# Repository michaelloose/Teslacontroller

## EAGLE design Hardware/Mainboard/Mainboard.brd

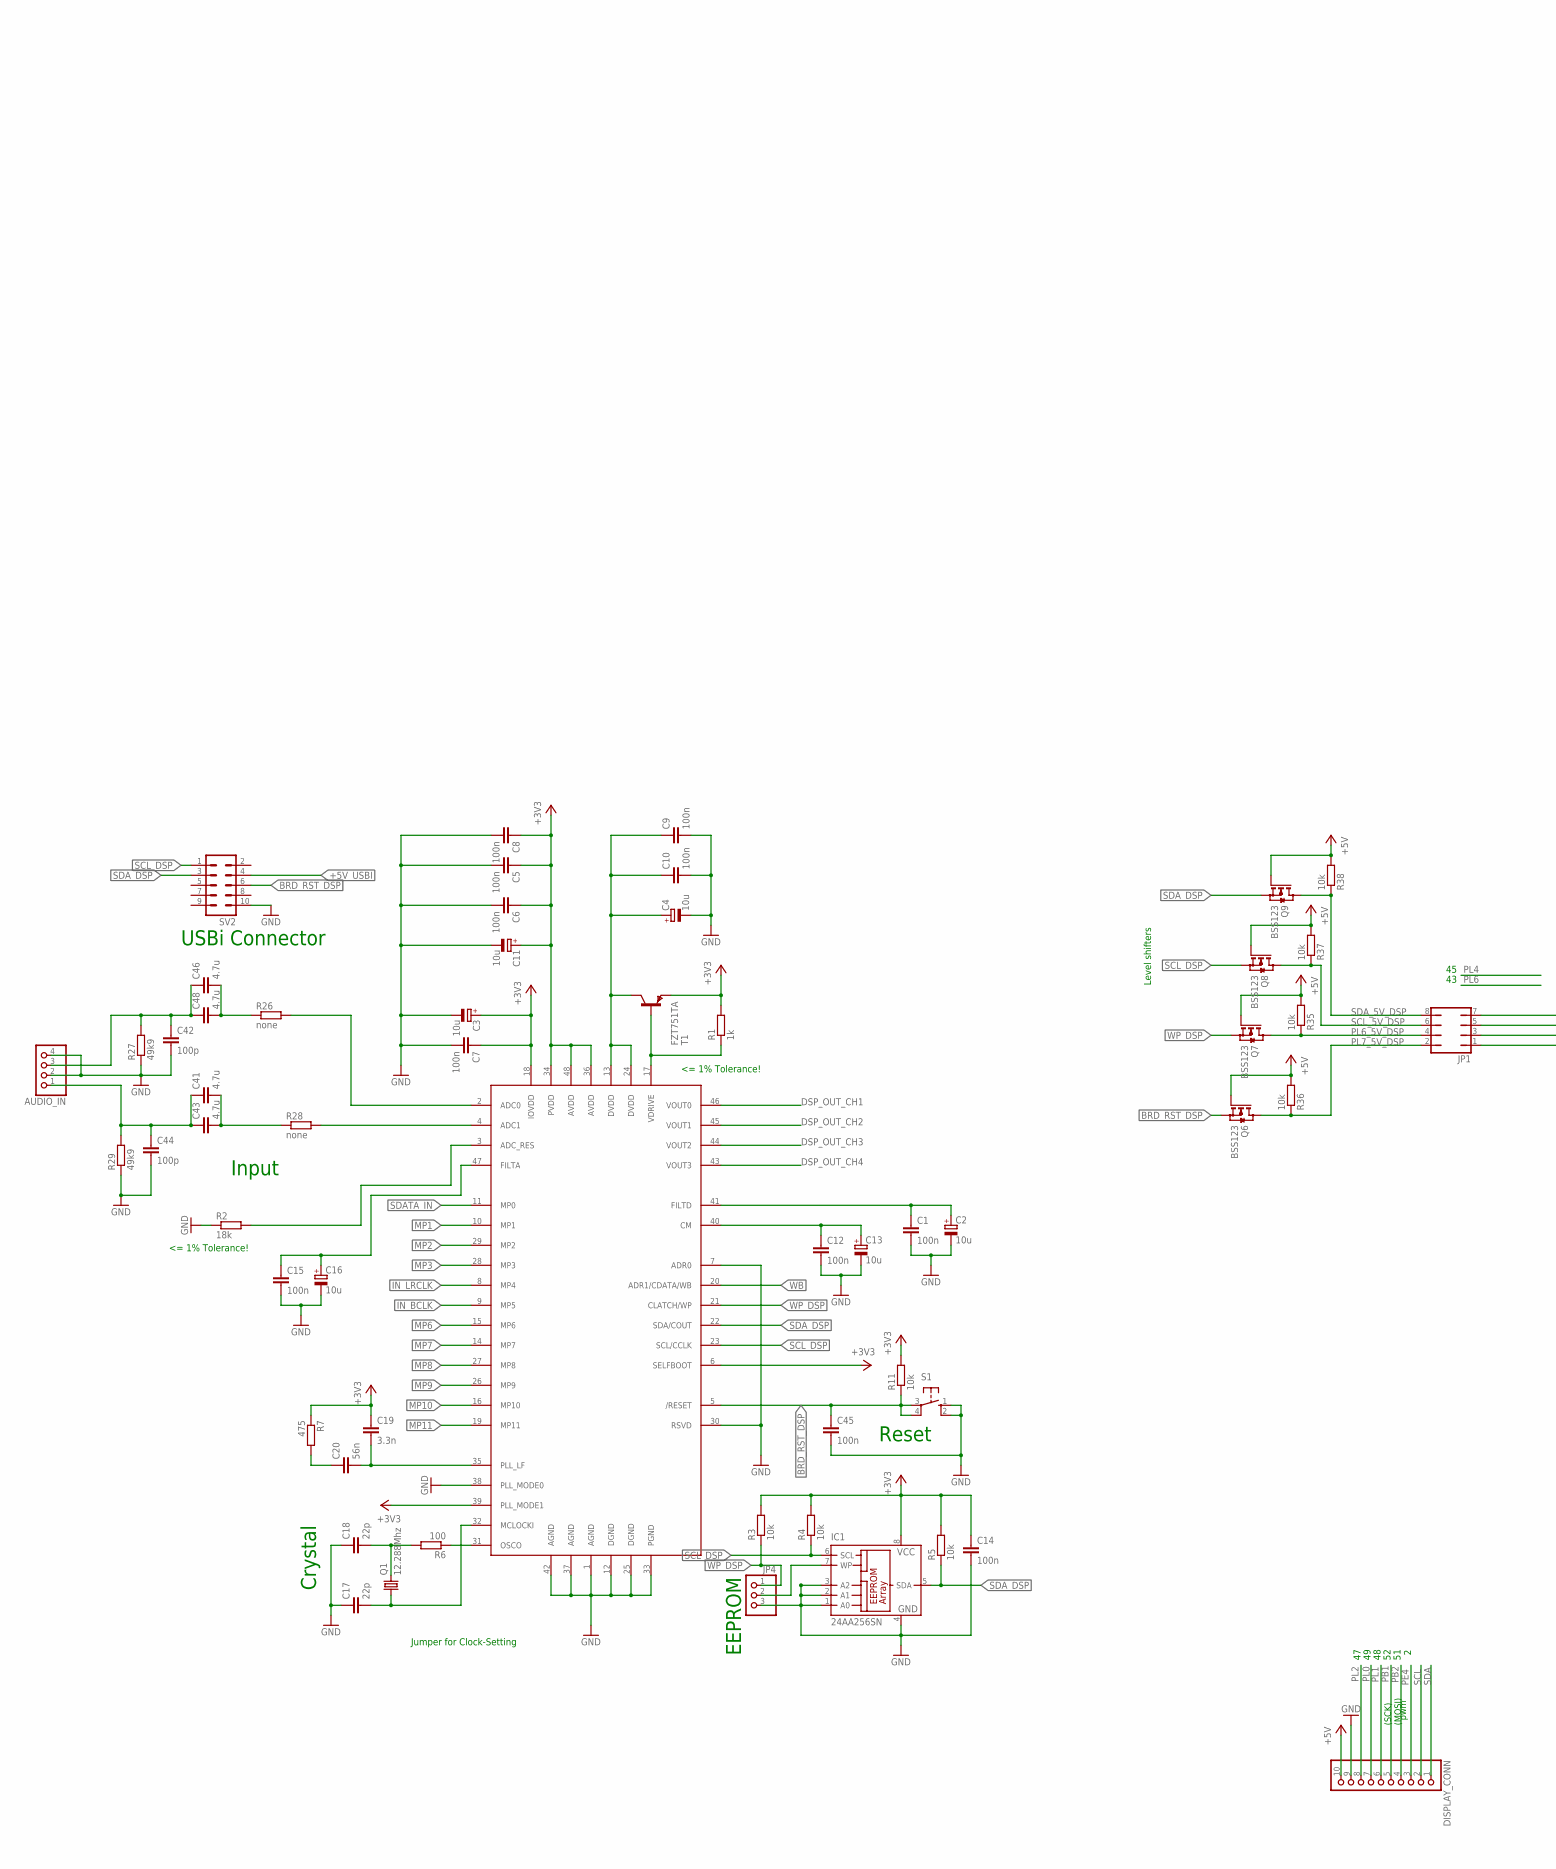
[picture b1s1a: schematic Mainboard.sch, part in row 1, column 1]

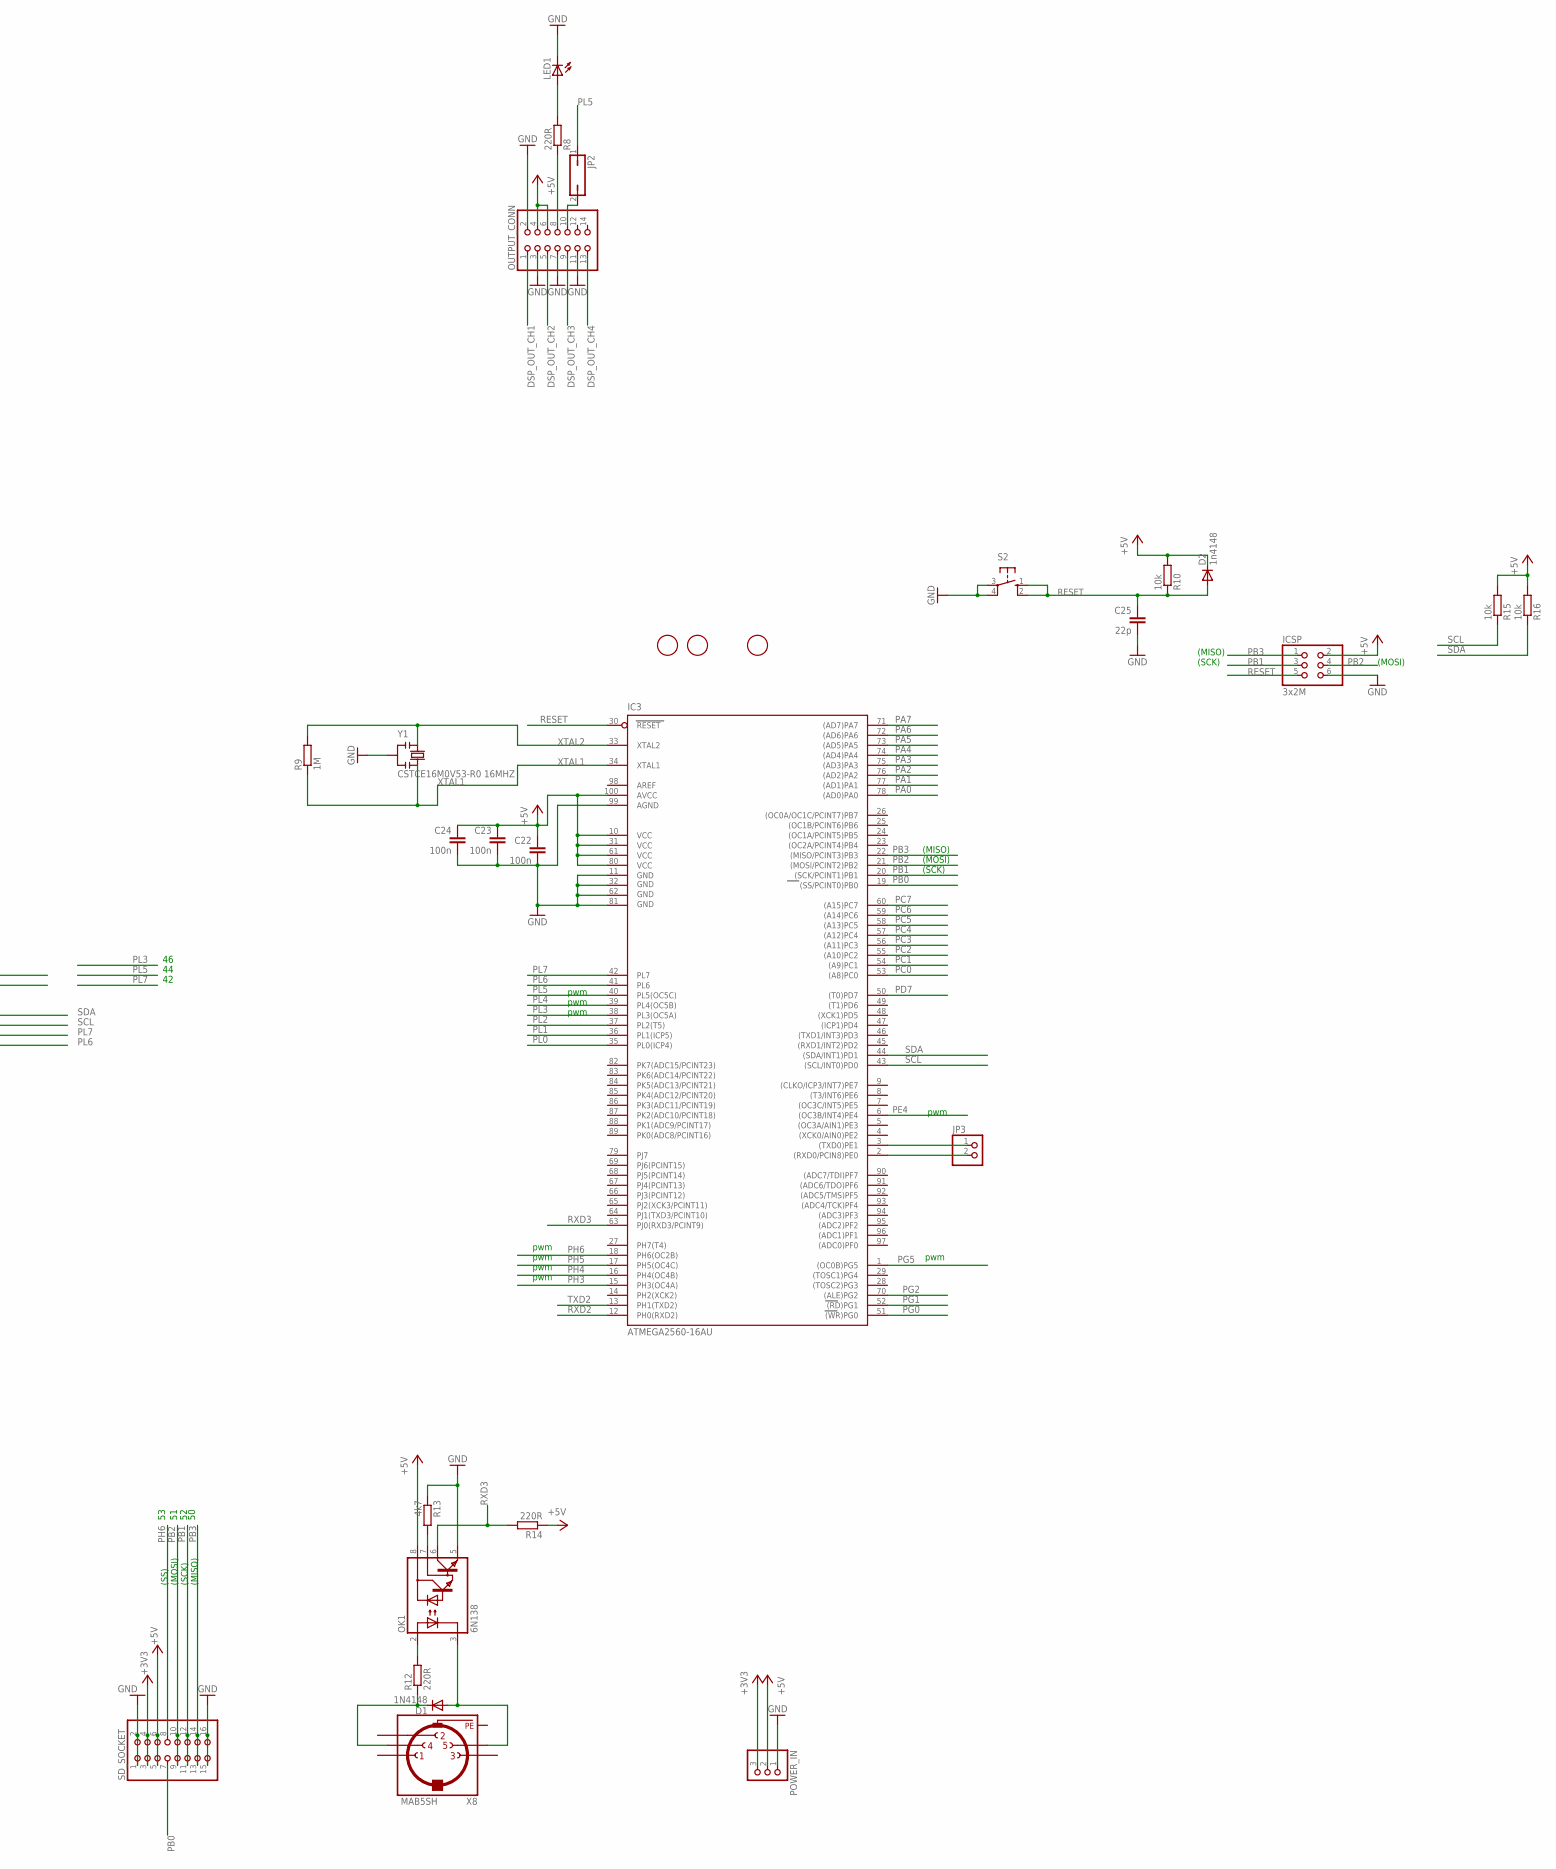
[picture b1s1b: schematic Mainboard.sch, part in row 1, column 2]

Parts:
AUDIO_IN: PINHD-1X4; 1X04
C1, C5, C6, C7, C8, C9, C10, C12, C14, C15, C22, C23, C24, C45: 100n; C0805K
C2, C3, C4, C11, C13, C16: 10u; E1,8-4
C17, C18, C25: 22p; C0805K
C19: 3.3n; C0805K
C20: 56n; C0805K
C41, C43, C46, C48: 4.7u; C050-075X075
C42, C44: 100p; C0805K
D1: 1N4148; SOD-123_MINI-SMA
D2: 1n4148; SOD-123_MINI-SMA
DISPLAY_CONN: PINHD-1X10; 1X10
FD1, FD2, FD4: FIDUCIALMOUNT; FIDUCIA-MOUNT
IC1: 24AA256SN; SO-08
IC3: ATMEGA2560-16AU; TQFP100
ICSP: 3x2M; 2X03
JP1: JP4Q
JP2: JP1Q; JP1
JP3: PINHD-1X2; 1X02
JP4: PINHD-1X3; 1X03
LED1: LED5MM
OK1: 6N138; DIL08
OUTPUT_CONN: PINHD-2X7; 2X07
POWER_IN: PINHD-1X3; 1X03
Q1: 12.288Mhz; HC49/S
Q6, Q7, Q8, Q9: BSS123; SOT23
R1: 1k; R0805
R2: 18k; R0805
R3, R4, R5, R10, R11, R15, R16, R35, R36, R37, R38: 10k; R0805
R6: 100; R0805
R7: 475; R0805
R8, R12, R14: 220R; R0805
R9: 1M; R0805
R13: 4k7; R0805
R26, R28: none; R0805
R27, R29: 49k9; R0805
S1, S2: 10-XX; B3F-10XX
SD_SOCKET: PINHD-2X8; 2X08
SV2: ML10
T1: FZT751TA; SOT223
U$1: ADAU1701; LQFP-48
X8: MAB5SH
Y1: CSTCE16M0V53-R0 16MHZ; RESONATOR

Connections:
1V8_DSP: C4.+, C9.1, C10.1, T1.2 (C), T1.4 (C), U$1.13 (DVDD), U$1.24 (DVDD)
+3V3: C3.+, C5.1, C6.1, C7.1, C8.1, C11.+, C14.1, C19.1, IC1.8 (VCC), POWER_IN.3, R1.2, R3.2, R4.2, R5.2, R7.1, R11.2, SD_SOCKET.3, SD_SOCKET.4, T1.3 (E), U$1.6 (SELFBOOT), U$1.18 (IOVDD), U$1.34 (PVDD), U$1.36 (AVDD), U$1.39 (PLL_MODE1), U$1.48 (AVDD)
+5V: C22.1, C23.1, C24.1, D2.C, DISPLAY_CONN.10, IC3.10 (VCC), IC3.31 (VCC1), IC3.61 (VCC2), IC3.80 (VCC3), IC3.100 (AVCC), ICSP.2, OK1.8 (VCC), OUTPUT_CONN.4, OUTPUT_CONN.6, POWER_IN.2, Q6.1 (G), Q7.1 (G), Q8.1 (G), Q9.1 (G), R10.2, R14.1, R15.2, R16.2, R35.2, R36.2, R37.2, R38.2, SD_SOCKET.5, SD_SOCKET.6
+5V_USBI: SV2.4
ADC0: R28.2, U$1.4 (ADC1)
BRD_RST_DSP: C45.1, Q6.2 (S), R11.1, S1.3, S1.4 (P1), SV2.6, U$1.5 (/RESET)
CM: C12.1, C13.+, U$1.40 (CM)
DSP_OUT_CH1: OUTPUT_CONN.1, U$1.46 (VOUT0)
DSP_OUT_CH2: OUTPUT_CONN.5, U$1.45 (VOUT1)
DSP_OUT_CH3: OUTPUT_CONN.9, U$1.44 (VOUT2)
DSP_OUT_CH4: OUTPUT_CONN.13, U$1.43 (VOUT3)
FILTA: C15.1, C16.+, U$1.47 (FILTA)
FILTD: C1.1, C2.+, U$1.41 (FILTD)
GND: AUDIO_IN.2, AUDIO_IN.4, C1.2, C2.-, C3.-, C4.-, C5.2, C6.2, C7.2, C8.2, C9.2, C10.2, C11.-, C12.2, C13.-, C14.2, C15.2, C16.-, C17.1, C18.1, C22.2, C23.2, C24.2, C25.2, C42.2, C44.2, C45.2, DISPLAY_CONN.9, IC1.1 (A0), IC1.2 (A1), IC1.3 (A2), IC1.4 (GND), IC3.11 (GND), IC3.32 (GND1), IC3.62 (GND2), IC3.81 (GND3), IC3.99 (AGND), ICSP.6, JP4.3, LED1.K (C), OK1.5 (GND), OUTPUT_CONN.2, OUTPUT_CONN.3, OUTPUT_CONN.7, OUTPUT_CONN.11, POWER_IN.1, R2.1, R13.1, R27.1, R29.1, S1.1 (S), S1.2 (S1), S2.3, S2.4 (P1), SD_SOCKET.1, SD_SOCKET.2, SD_SOCKET.15, SD_SOCKET.16, SV2.10, U$1.1 (AGND), U$1.7 (ADR0), U$1.12 (DGND), U$1.25 (DGND), U$1.30 (RSVD), U$1.33 (PGND), U$1.37 (AGND), U$1.38 (PLL_MODE0), U$1.42 (AGND), Y1.2
IN_BCLK: U$1.9 (MP5)
IN_LRCLK: U$1.8 (MP4)
MP1: U$1.10 (MP1)
MP2: U$1.29 (MP2)
MP3: U$1.28 (MP3)
MP6: U$1.15 (MP6)
MP7: U$1.14 (MP7)
MP8: U$1.27 (MP8)
MP9: U$1.26 (MP9)
MP10: U$1.16 (MP10)
MP11: U$1.19 (MP11)
unnamed: R2.2, U$1.3 (ADC_RES)
unnamed: R1.1, T1.1 (B), U$1.17 (VDRIVE)
unnamed: C19.2, C20.2, U$1.35 (PLL_LF)
unnamed: OUTPUT_CONN.8, R8.1
unnamed: C20.1, R7.2
unnamed: C18.2, Q1.2, R6.2
unnamed: C17.2, Q1.1, U$1.32 (MCLOCKI)
unnamed: R6.1, U$1.31 (OSCO)
unnamed: LED1.A, R8.2
unnamed: JP2.2, OUTPUT_CONN.10
unnamed: IC3.3 ((TXD0)PE1), JP3.1
unnamed: IC3.2 ((RXD0/PCIN8)PE0), JP3.2
unnamed: OK1.2 (A), R12.2
unnamed: D1.C, R12.1, X8.4
unnamed: D1.A, OK1.3 (C), X8.5
unnamed: OK1.7 (VB), R13.2
unnamed: C46.2, C48.2, R26.1
unnamed: AUDIO_IN.3, C42.1, C46.1, C48.1, R27.2
unnamed: AUDIO_IN.1, C41.1, C43.1, C44.1, R29.2
unnamed: C41.2, C43.2, R28.1
unnamed: R26.2, U$1.2 (ADC0)
unnamed: IC1.7 (WP), JP4.2
PA0: IC3.78 ((AD0)PA0)
PA1: IC3.77 ((AD1)PA1)
PA2: IC3.76 ((AD2)PA2)
PA3: IC3.75 ((AD3)PA3)
PA4: IC3.74 ((AD4)PA4)
PA5: IC3.73 ((AD5)PA5)
PA6: IC3.72 ((AD6)PA6)
PA7: IC3.71 ((AD7)PA7)
PB0: IC3.19 ((SS/PCINT0)PB0), SD_SOCKET.7
PB1: DISPLAY_CONN.5, IC3.20 ((SCK/PCINT1)PB1), ICSP.3, SD_SOCKET.11, SD_SOCKET.12
PB2: DISPLAY_CONN.4, IC3.21 ((MOSI/PCINT2)PB2), ICSP.4, SD_SOCKET.9, SD_SOCKET.10
PB3: IC3.22 ((MISO/PCINT3)PB3), ICSP.1, SD_SOCKET.13, SD_SOCKET.14
PC0: IC3.53 ((A8)PC0)
PC1: IC3.54 ((A9)PC1)
PC2: IC3.55 ((A10)PC2)
PC3: IC3.56 ((A11)PC3)
PC4: IC3.57 ((A12)PC4)
PC5: IC3.58 ((A13)PC5)
PC6: IC3.59 ((A14)PC6)
PC7: IC3.60 ((A15)PC7)
PD7: IC3.50 ((T0)PD7)
PE: X8.PE, X8.PE@ (PE)
PE4: DISPLAY_CONN.3, IC3.6 ((OC3B/INT4)PE4)
PG0: IC3.51 ((WR)PG0)
PG1: IC3.52 ((RD)PG1)
PG2: IC3.70 ((ALE)PG2)
PG5: IC3.1 ((OC0B)PG5)
PH3: IC3.15 (PH3(OC4A))
PH4: IC3.16 (PH4(OC4B))
PH5: IC3.17 (PH5(OC4C))
PH6: IC3.18 (PH6(OC2B)), SD_SOCKET.8
PL0: DISPLAY_CONN.7, IC3.35 (PL0(ICP4))
PL1: DISPLAY_CONN.6, IC3.36 (PL1(ICP5))
PL2: DISPLAY_CONN.8, IC3.37 (PL2(T5))
PL3: IC3.38 (PL3(OC5A))
PL4: IC3.39 (PL4(OC5B))
PL5: IC3.40 (PL5(OC5C)), JP2.1
PL6: IC3.41 (PL6), JP1.1
PL6_5V_DSP: JP1.4, Q7.3 (D), R35.1
PL7: IC3.42 (PL7), JP1.3
PL7_5V_DSP: JP1.2, Q6.3 (D), R36.1
RESET: C25.1, D2.A, IC3.30 (RESET), ICSP.5, R10.1, S2.1 (S), S2.2 (S1)
RXD2: IC3.12 (PH0(RXD2))
RXD3: IC3.63 (PJ0(RXD3/PCINT9)), OK1.6 (VO), R14.2
SCL: DISPLAY_CONN.2, IC3.43 ((SCL/INT0)PD0), JP1.5, R15.1
SCL_5V_DSP: JP1.6, Q8.3 (D), R37.1
SCL_DSP: IC1.6 (SCL), Q8.2 (S), R4.1, SV2.1, U$1.23 (SCL/CCLK)
SDA: DISPLAY_CONN.1, IC3.44 ((SDA/INT1)PD1), JP1.7, R16.1
SDATA_IN: U$1.11 (MP0)
SDA_5V_DSP: JP1.8, Q9.3 (D), R38.1
SDA_DSP: IC1.5 (SDA), Q9.2 (S), R5.1, SV2.3, U$1.22 (SDA/COUT)
TXD2: IC3.13 (PH1(TXD2))
WB: U$1.20 (ADR1/CDATA/WB)
WP_DSP: JP4.1, Q7.2 (S), R3.1, U$1.21 (CLATCH/WP)
XTAL1: IC3.34 (XTAL1), R9.1, Y1.3
XTAL2: IC3.33 (XTAL2), R9.2, Y1.1

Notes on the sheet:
<= 1% Tolerance!
EEPROM
Jumper for Clock-Setting
Crystal
Reset
Input
USBi Connector
Level shifters
(SCK)
(MISO)
(MOSI)
pwm
(SS)

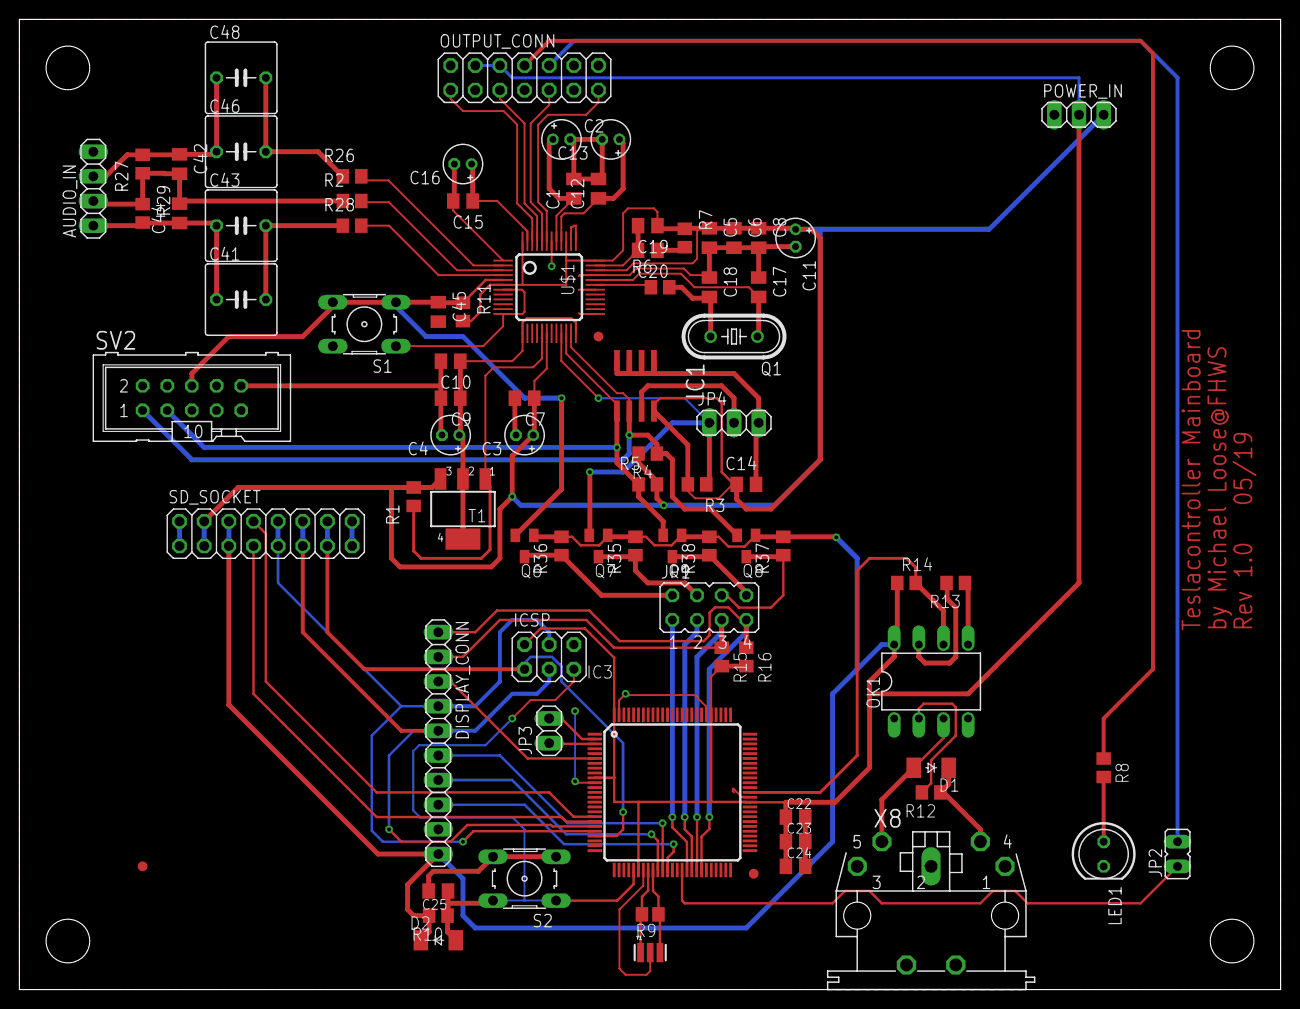
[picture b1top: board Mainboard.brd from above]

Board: 2 copper layers, 130.0 x 100.0 mm, 86 parts (0 on the bottom side), 61 nets.

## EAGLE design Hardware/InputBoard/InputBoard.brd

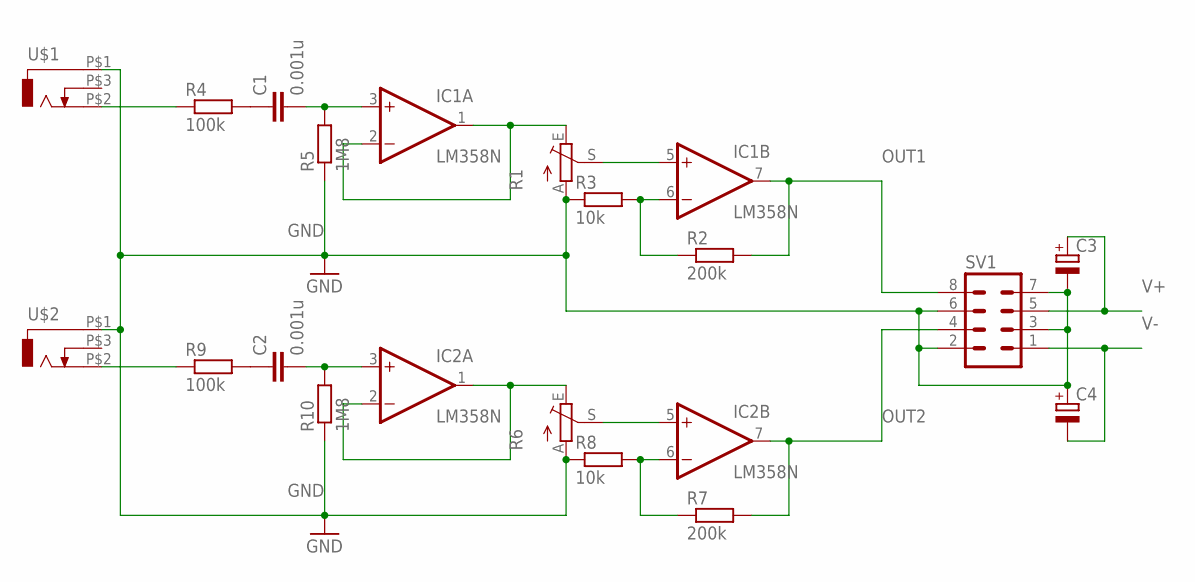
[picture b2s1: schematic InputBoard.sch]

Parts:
C1, C2: 0.001u; C050-025X075
C3, C4: CPOL-EUE5-8.5; E5-8,5
IC1, IC2: LM358N; DIL08
R1, R6: TRIM_EU-CIP20C-6MM; CIP20C-6MM
R2, R7: 200k; 0207/10
R3, R8: 10k; 0207/10
R4, R9: 100k; 0207/10
R5, R10: 1M8; 0207/10
SV1: MA04-2
U$1, U$2: EBS63P

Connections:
GND: C3.-, C4.+, R1.A, R3.1, R5.1, R6.A, R8.1, R10.1, SV1.2, SV1.3, SV1.6, SV1.7, U$1.P$1 (1), U$2.P$1 (1)
unnamed: IC1.1 (OUT), IC1.2 (-IN), R1.E
unnamed: IC1.5 (+IN), R1.S
unnamed: IC1.6 (-IN), R2.1, R3.2
unnamed: C1.2, IC1.3 (+IN), R5.2
unnamed: C1.1, R4.2
unnamed: IC2.1 (OUT), IC2.2 (-IN), R6.E
unnamed: IC2.5 (+IN), R6.S
unnamed: IC2.6 (-IN), R7.1, R8.2
unnamed: C2.2, IC2.3 (+IN), R10.2
unnamed: C2.1, R9.2
unnamed: R9.1, U$2.P$2 (3)
unnamed: R4.1, U$1.P$2 (3)
OUT1: IC1.7 (OUT), R2.2, SV1.8
OUT2: IC2.7 (OUT), R7.2, SV1.4
V+: C3.+, IC1.8 (V+), IC2.8 (V+), SV1.5
V-: C4.-, IC1.4 (V-), IC2.4 (V-), SV1.1

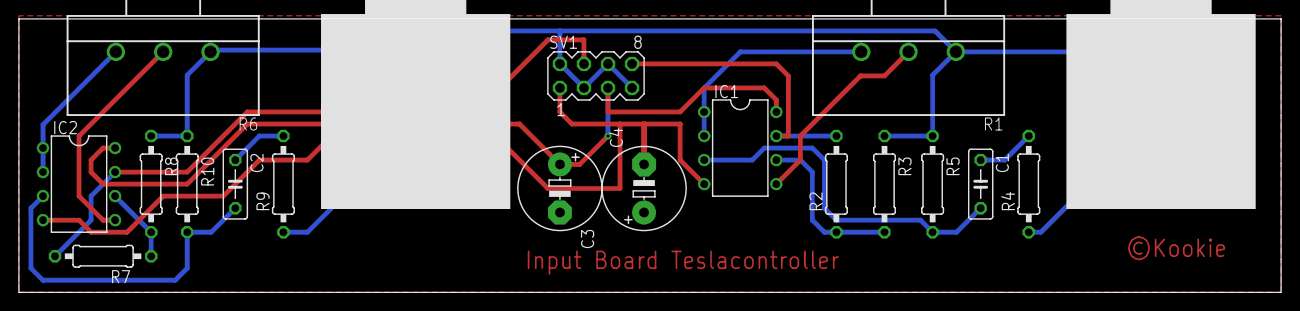
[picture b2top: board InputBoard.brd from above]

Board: 2 copper layers, 133.3 x 28.9 mm, 19 parts (0 on the bottom side), 17 nets.

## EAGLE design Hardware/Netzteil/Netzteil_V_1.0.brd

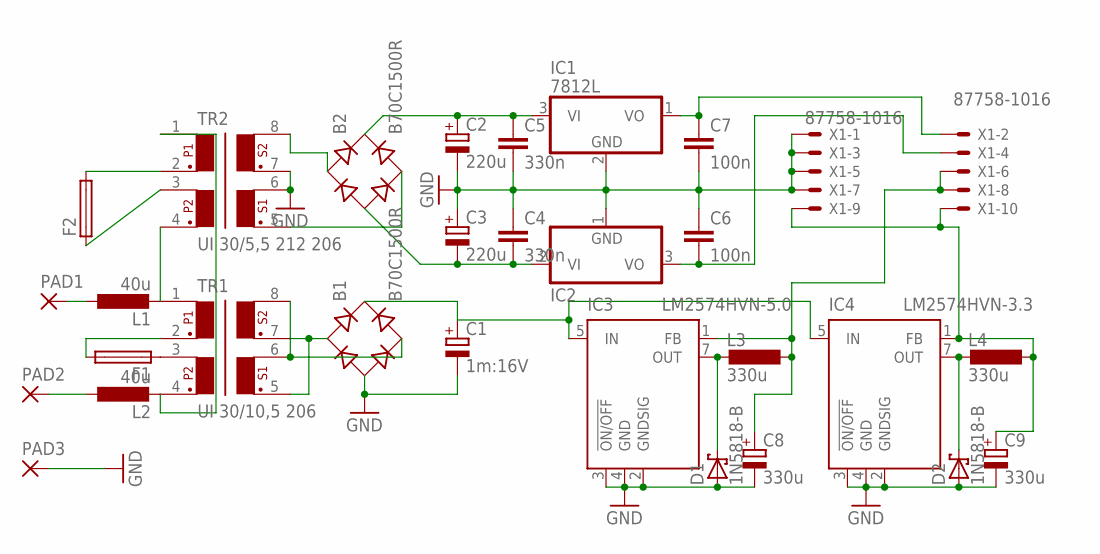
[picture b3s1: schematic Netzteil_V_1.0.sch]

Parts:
B1, B2: B70C1500R; RB1A
C1: 1m:16V; E5-13
C2, C3: 220u; E5-10,5
C4, C5: 330n; C102-064X133
C6: 100n; C102-064X133
C7: 100n; C102-054X133
C8, C9: 330u; E2,5-7
D1, D2: 1N5818-B; DO41-7.6
F1, F2: SH25
IC1: 7812L; TO92
IC2: 7912L; TO92
IC3: LM2574HVN-5.0; DIL08
IC4: LM2574HVN-3.3; DIL08
L1, L2: 40u; IRF24
L3, L4: 330u; 0207/5V
PAD1, PAD2, PAD3: 3,81/1,4
TR1: UI 30/10,5 206; FL02-08
TR2: UI 30/5,5 212 206; FL02-08
X1: 87758-1016

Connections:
3V3: C9.+, IC4.1 (FB), L4.1, X1.9, X1.10
5V: C8.+, IC3.1 (FB), L3.1, X1.6, X1.8
+12V: C7.1, IC1.1 (VO), X1.2
-12V: C6.2, IC2.3 (VO), X1.4
GND: B1.-, C1.-, C2.-, C3.+, C4.1, C5.2, C6.1, C7.2, C8.-, C9.-, D1.A, D2.A, IC1.2 (GND), IC2.1 (GND), IC3.2 (GNDSIG), IC3.3 (!ON/OFF), IC3.4 (GND), IC4.2 (GNDSIG), IC4.3 (!ON/OFF), IC4.4 (GND), PAD3.1, TR2.6, TR2.7, X1.1, X1.3, X1.5, X1.7
unnamed: F1.1, TR1.3
unnamed: F1.2, TR1.2
unnamed: B1.AC1, TR1.5, TR1.7
unnamed: B1.AC2, TR1.6, TR1.8
unnamed: B1.+, C1.+, IC3.5 (IN), IC4.5 (IN)
unnamed: B2.-, C3.-, C4.2, IC2.2 (VI)
unnamed: L1.2, TR1.1, TR2.4
unnamed: L2.2, TR1.4, TR2.1
unnamed: D1.C, IC3.7 (OUT), L3.2
unnamed: B2.AC1, TR2.8
unnamed: B2.AC2, TR2.5
unnamed: B2.+, C2.+, C5.1, IC1.3 (VI)
unnamed: F2.1, TR2.3
unnamed: F2.2, TR2.2
unnamed: D2.C, IC4.7 (OUT), L4.2
unnamed: L1.1, PAD1.1
unnamed: L2.1, PAD2.1

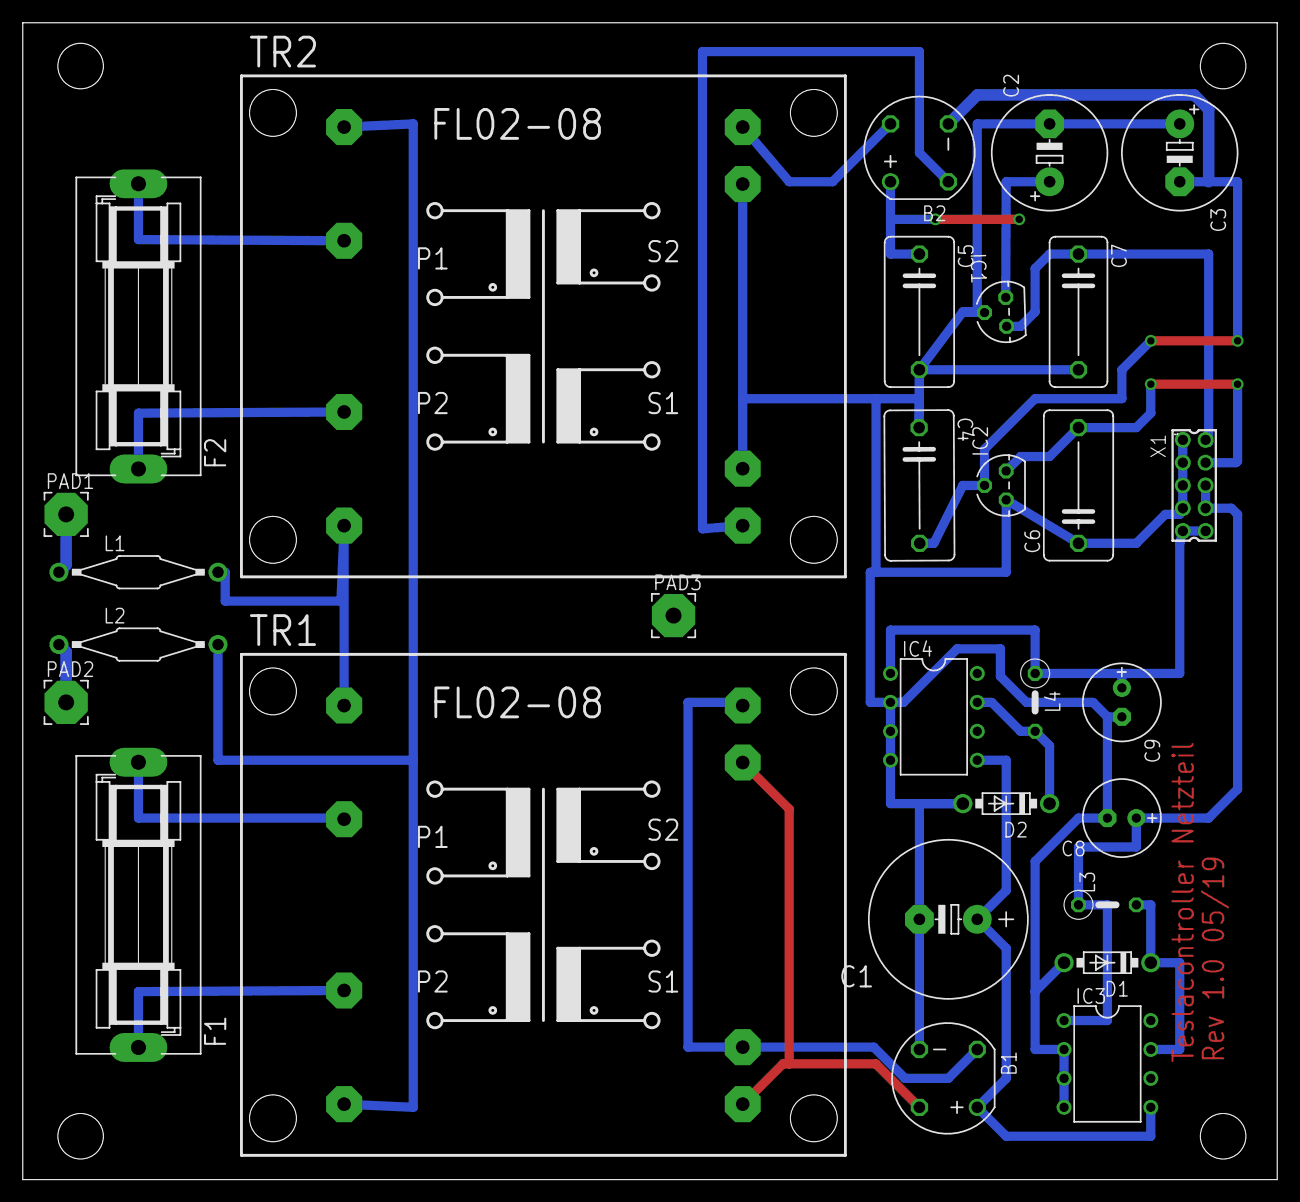
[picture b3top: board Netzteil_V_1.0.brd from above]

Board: 2 copper layers, 110.2 x 101.6 mm, 29 parts (0 on the bottom side), 22 nets.

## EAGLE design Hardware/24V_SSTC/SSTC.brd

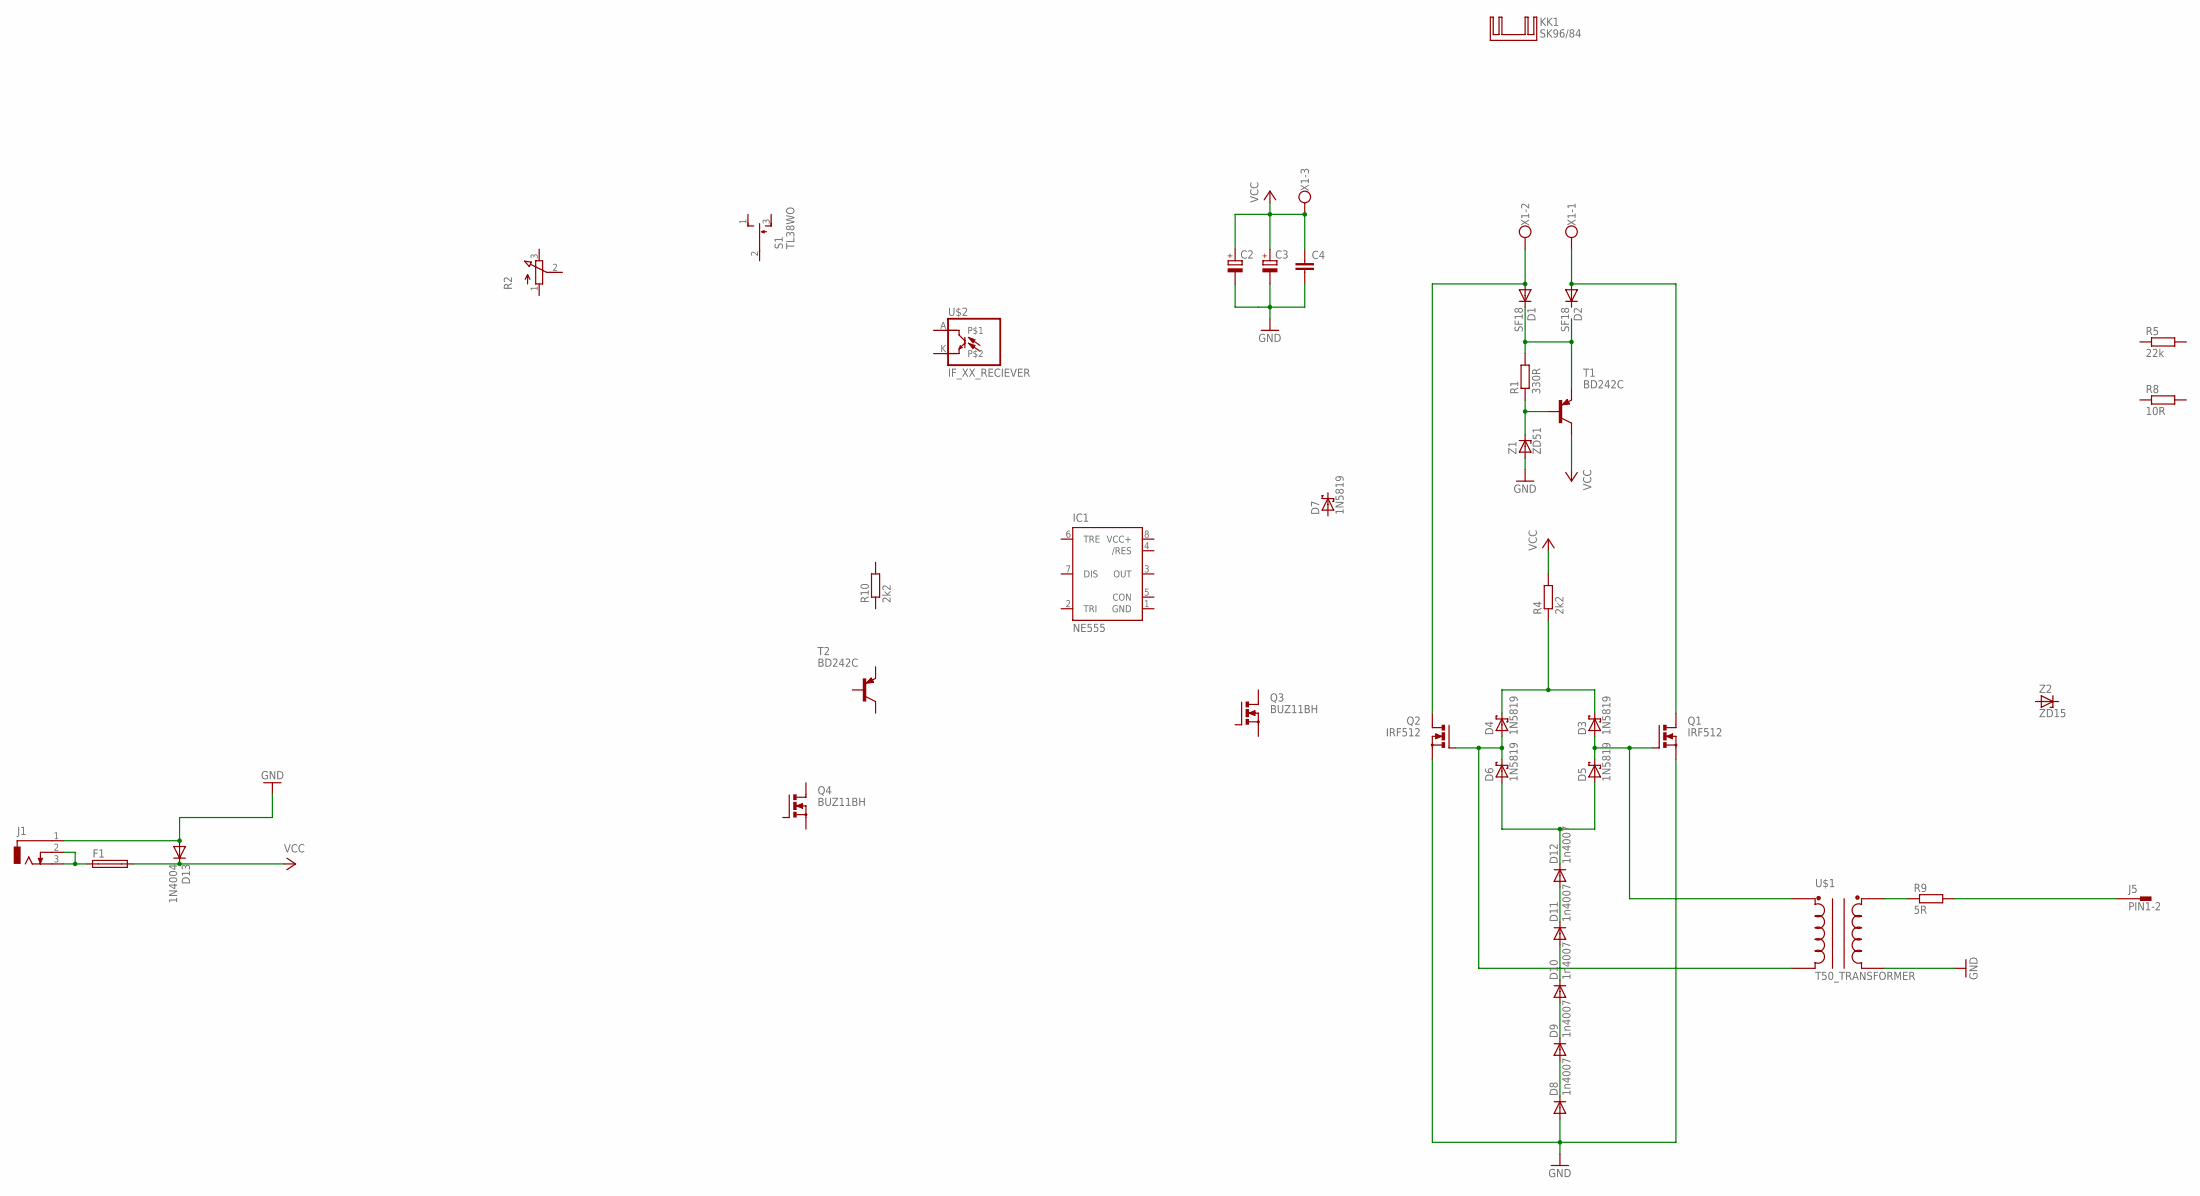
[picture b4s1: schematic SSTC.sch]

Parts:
C2, C3: CPOL-EUE7.5-18; E7,5-18
C4: C-EU150-072X183; C150-072X183
D1, D2: SF18; DO41-7.6
D3, D4, D5, D6, D7: 1N5819; SMB
D8, D9, D10, D11, D12: 1n4007; MELF-MLL41
D13: 1N4004; DO41-10
F1: SH22,5A
IC1: NE555; DIL-08
J1: DCJ0303
J5: PIN1-2; 62221
KK1: SK96/84
Q1, Q2: IRF512; TO220BV
Q3, Q4: BUZ11BH; TO220BH
R1: 330R; R2512
R2: 3RP/1610N
R4, R10: 2k2; R2512
R5: 22k; R2512
R8: 10R; R2512
R9: 5R; 0309/12
S1: TL38WO; TL3XWO
T1, T2: BD242C; TO220V
U$1: T50_TRANSFORMER
U$2: IF_XX_RECIEVER; IF_XX
X1: W237-103
Z1: ZD51; SOD80C
Z2: ZD15; SOD80C

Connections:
GND: C2.-, C3.-, C4.2, D8.A, D13.A, IC1.1 (GND), J1.1, Q1.S, Q2.S, U$1.C2A, Z1.A
unnamed: D8.C, D9.A
unnamed: D9.C, D10.A
unnamed: D10.C, D11.A
unnamed: D11.C, D12.A
unnamed: D5.A, D6.A, D12.C
unnamed: D4.A, D6.C, Q2.G, U$1.C1A
unnamed: D3.A, D5.C, Q1.G, U$1.C1B
unnamed: D1.A, Q2.D, X1.2
unnamed: D2.A, Q1.D, X1.1
unnamed: D3.C, D4.C, R4.1
unnamed: D1.C, R1.2, T1.3 (E)
unnamed: R1.1, T1.1 (B), Z1.C
unnamed: R9.1, U$1.C2B
unnamed: J5.1, R9.2
unnamed: F1.1, J1.2, J1.3
VCC: C2.+, C3.+, C4.1, D13.C, F1.2, R4.2, T1.2 (C), X1.3
VCC+: IC1.8 (VCC+)

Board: 2 copper layers, 40 parts (0 on the bottom side), 17 nets, no tracks yet.

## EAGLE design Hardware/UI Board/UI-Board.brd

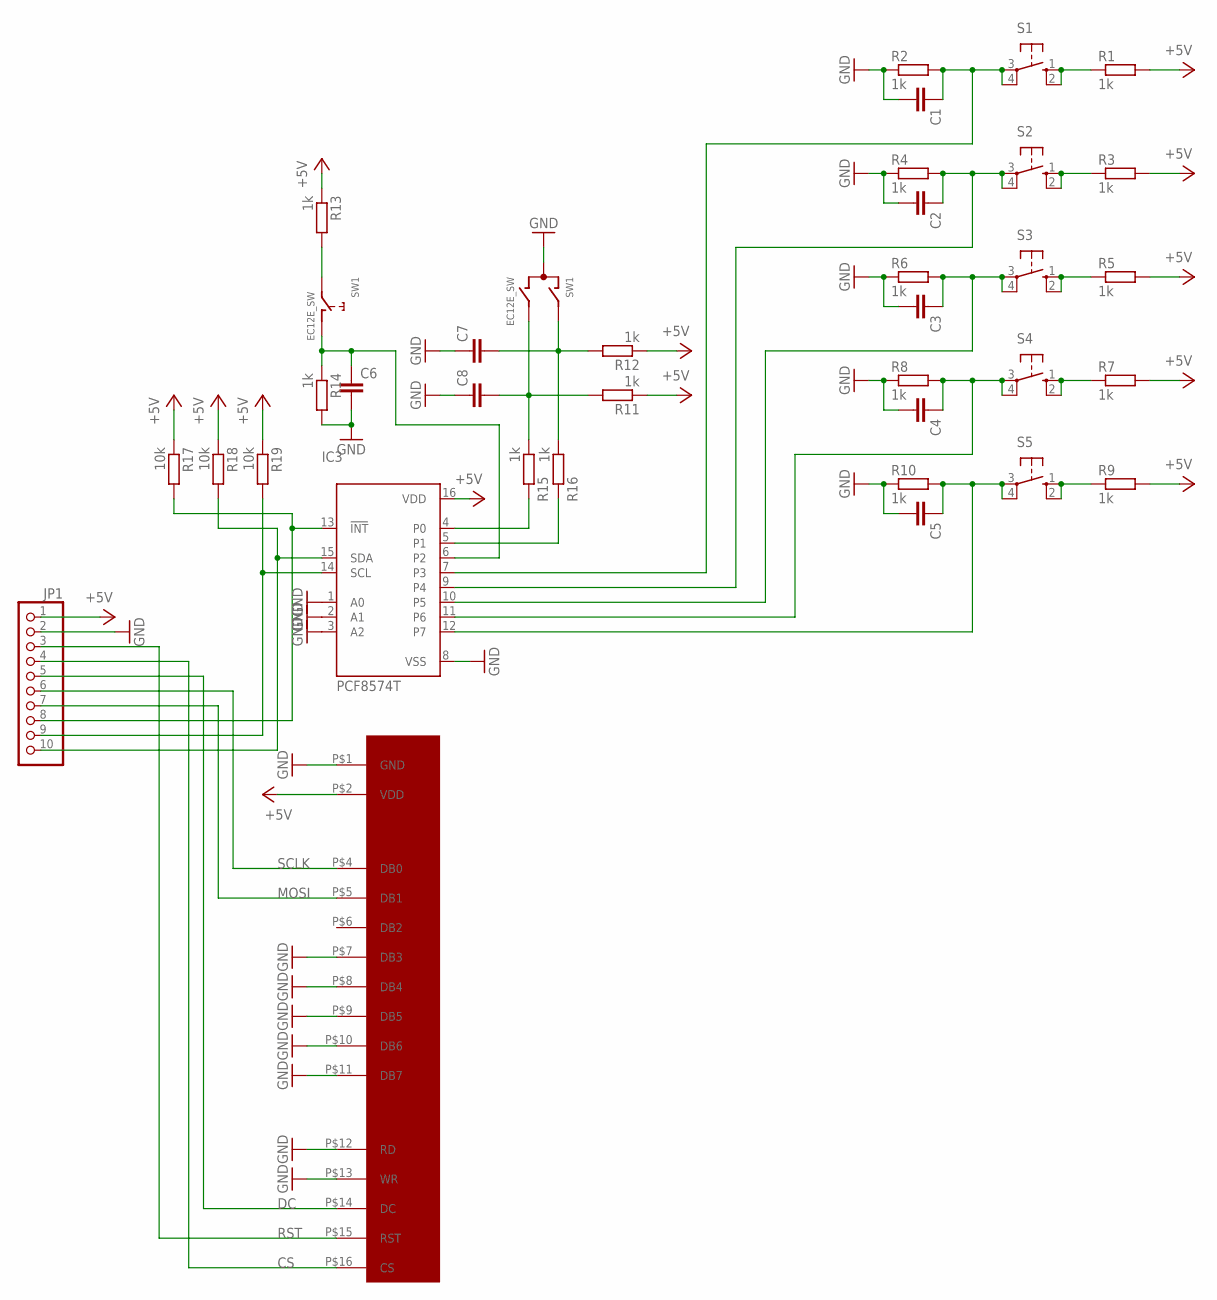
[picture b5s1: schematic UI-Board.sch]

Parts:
C1, C2, C3, C4, C5, C6, C7, C8: C-EUC0805; C0805
IC3: PCF8574T; SO16W
JP1: PINHD-1X10/90; 1X10/90
R1, R2, R3, R4, R5, R6, R7, R8, R9, R10, R11, R12, R13, R14, R15, R16: 1k; R0805
R17, R18, R19: 10k; R0805
S1, S2, S3, S4, S5: 10-XX; B3F-10XX
SW1: EC12E_SW; ALPS_EC12E_SW
U$1: OLED64X256

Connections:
+5V: IC3.16 (VDD), JP1.1, R1.2, R3.2, R5.2, R7.2, R9.2, R11.1, R12.1, R13.1, R17.1, R18.1, R19.1, U$1.P$2 (VDD)
CS: JP1.4, U$1.P$16 (CS)
DC: JP1.5, U$1.P$14 (DC)
GND: C1.2, C2.2, C3.2, C4.2, C5.2, C6.2, C7.1, C8.1, IC3.1 (A0), IC3.2 (A1), IC3.3 (A2), IC3.8 (VSS), JP1.2, R2.1, R4.1, R6.1, R8.1, R10.1, R14.2, SW1.C, U$1.P$1 (GND), U$1.P$7 (DB3), U$1.P$8 (DB4), U$1.P$9 (DB5), U$1.P$10 (DB6), U$1.P$11 (DB7), U$1.P$12 (RD), U$1.P$13 (WR)
INT: IC3.13 (!INT), JP1.8, R17.2
MOSI: JP1.7, U$1.P$5 (DB1)
unnamed: R1.1, S1.1 (S), S1.2 (S1)
unnamed: R3.1, S2.1 (S), S2.2 (S1)
unnamed: R5.1, S3.1 (S), S3.2 (S1)
unnamed: R7.1, S4.1 (S), S4.2 (S1)
unnamed: R9.1, S5.1 (S), S5.2 (S1)
unnamed: IC3.4 (P0), R15.2
unnamed: C5.1, IC3.12 (P7), R10.2, S5.3, S5.4 (P1)
unnamed: C4.1, IC3.11 (P6), R8.2, S4.3, S4.4 (P1)
unnamed: C3.1, IC3.10 (P5), R6.2, S3.3, S3.4 (P1)
unnamed: C2.1, IC3.9 (P4), R4.2, S2.3, S2.4 (P1)
unnamed: C1.1, IC3.7 (P3), R2.2, S1.3, S1.4 (P1)
unnamed: IC3.5 (P1), R16.2
unnamed: C8.2, R11.2, R15.1, SW1.B
unnamed: C7.2, R12.2, R16.1, SW1.A
unnamed: C6.1, IC3.6 (P2), R14.1, SW1.D (1)
unnamed: R13.2, SW1.E (2)
RST: JP1.3, U$1.P$15 (RST)
SCL: IC3.14 (SCL), JP1.9, R19.2
SCLK: JP1.6, U$1.P$4 (DB0)
SDA: IC3.15 (SDA), JP1.10, R18.2

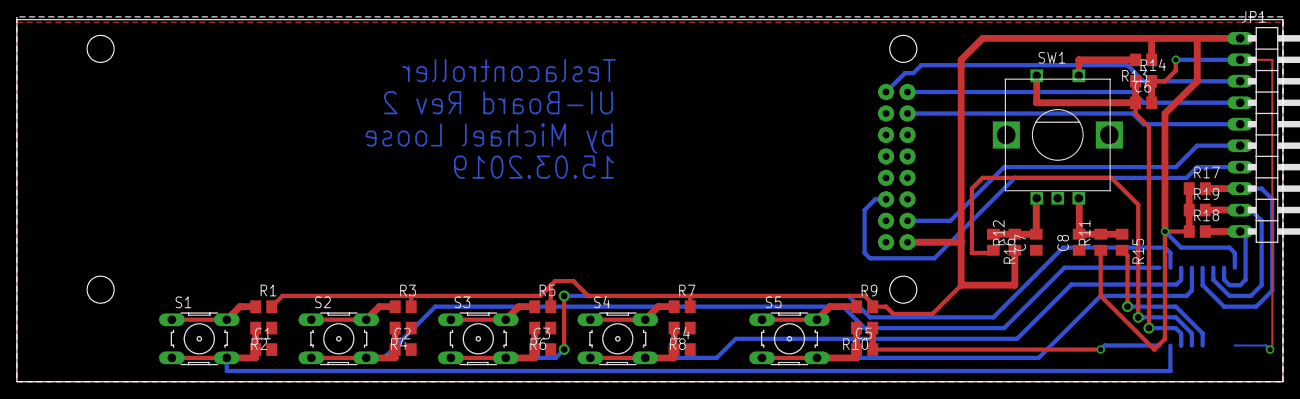
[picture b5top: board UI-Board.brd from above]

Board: 2 copper layers, 149.9 x 43.2 mm, 36 parts (1 on the bottom side), 26 nets.

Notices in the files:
Hardware/InputBoard/InputBoard.brd:
©Kookie
parts and their libraries:
SparkFun-IC-Amplifiers: Licensing: Creative Commons ShareAlike 4.0 International - https://creativecommons.org/licenses/by-sa/4.0
